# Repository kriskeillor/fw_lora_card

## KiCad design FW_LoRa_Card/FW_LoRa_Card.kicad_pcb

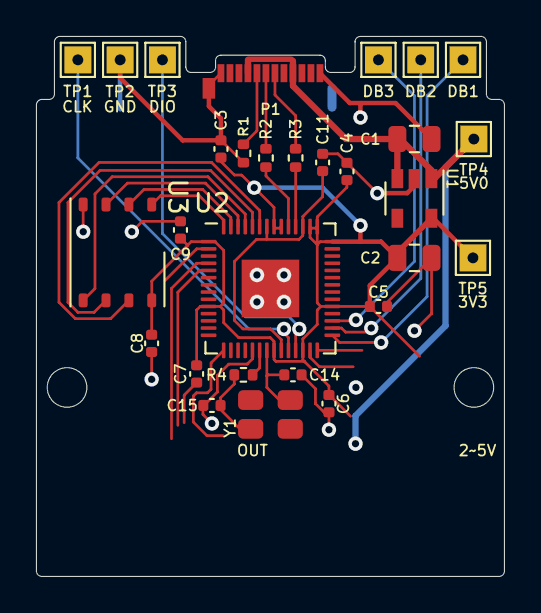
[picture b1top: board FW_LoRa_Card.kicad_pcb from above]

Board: 2 copper layers, 26.0 x 30.0 mm, 31 parts (0 on the bottom side), 23 nets.

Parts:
C1, C2: 10uF; C_0805_2012Metric
C3, C4, C5, C6, C7, C8, C9, C11: 10nF; C_0402_1005Metric
C14, C15: 8pF; C_0402_1005Metric
DB1, DB2, DB3: TestPoint; TestPoint_Pad_1.5x1.5mm_THT
H1, H2: MountingHole; MountingHole_2.2mm_M2
P1: USB_C_Plug_USB2.0; USB_C_Plug_Molex_105444
R1: 5.1k; R_0402_1005Metric
R2, R3, R4: 1.2k; R_0402_1005Metric
TP1, TP2, TP3, TP4, TP5: TestPoint; TestPoint_Pad_1.5x1.5mm_THT
U1: AP2112K-3.3; SOT-23-5
U2: RP2040; QFN-56-1EP_7x7mm_P0.4mm_EP3.2x3.2mm
U3: W25Q128JVS; WSON-8-1EP_6x5mm_P1.27mm_EP3.4x4mm
Y1: RH100-12.000-9-1015-TR-NS1; 4-SMD_3.2mm-x-2.5mm

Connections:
+1V1: C11.1, U2.23 (DVDD), U2.45 (VREG_VOUT), U2.50 (DVDD)
+3V3: C2.1, C3.1, C4.1, C5.1, C6.1, C7.2, C8.1, C9.1, TP5.1, U1.5 (VOUT), U2.1 (IOVDD), U2.10 (IOVDD), U2.22 (IOVDD), U2.26 (RUN), U2.33 (IOVDD), U2.42 (IOVDD), U2.43 (ADC_AVDD), U2.44 (VREG_IN), U2.48 (USB_VDD), U2.49 (IOVDD), U3.8 (VCC)
/DEBUG1: DB1.1, U2.29 (GPIO18)
/DEBUG2: DB2.1, U2.30 (GPIO19)
/DEBUG3: DB3.1, U2.31 (GPIO20)
/MEM_CLK: U2.52 (QSPI_SCLK), U3.6 (CLK)
/MEM_CS_N: U2.56 (QSPI_SS), U3.1 (~CS)
/MEM_D0: U2.53 (QSPI_SD0), U3.5 (DI(IO0))
/MEM_D1: U2.55 (QSPI_SD1), U3.2 (DO(IO1))
/MEM_D2: U2.54 (QSPI_SD2), U3.3 (IO2)
/MEM_D3: U2.51 (QSPI_SD3), U3.7 (IO3)
/SWCLK_IN: TP1.1, U2.24 (SWCLK)
/SWDIO_IN: TP3.1, U2.25 (SWD)
/USB_D_N: R3.1, U2.46 (USB_DM)
/USB_D_P: R2.1, U2.47 (USB_DP)
/USB_N: P1.A7 (D-), R3.2
/USB_P: P1.A6 (D+), R2.2
/XI: R4.1, U2.20 (XIN)
/YI: C14.1, U2.21 (XOUT), Y1.3
/YO: C15.1, R4.2, Y1.1
GND: C1.2, C2.2, C3.2, C4.2, C5.2, C6.2, C7.1, C8.2, C9.2, C11.2, C14.2, C15.2, P1.A1 (GND), P1.A12 (GND), P1.B1 (GND), P1.B12 (GND), P1.S1 (SHIELD), R1.2, TP2.1, U1.2 (GND), U2.19 (TESTEN), U2.57 (GND), U3.4 (GND)
unnamed: P1.A5 (CC), R1.1
VBUS: C1.1, P1.A4 (VBUS), P1.A9 (VBUS), P1.B4 (VBUS), P1.B9 (VBUS), TP4.1, U1.1 (VIN), U1.3 (EN)

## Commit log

2023-03-20 copy of fw_rp-2040_probe

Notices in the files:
FW_LoRa_Card/FW_LoRa_Card.kicad_pcb:
This work is licensed under a Creative Commons Attribution 4.0 International License
